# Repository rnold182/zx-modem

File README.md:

# ZX MODEM

A Wi-Fi network modem for an **unmodified ZX Spectrum 48K**. An ESP32 talks
to the Spectrum through its **EAR and MIC tape sockets**, using the
Spectrum's own ROM tape routines in both directions: no hardware changes, no
expansion port, no custom Spectrum audio code.

On top of it runs a small app platform: a menu with a live status line
(network, signal, IP, date and time), a Wi-Fi setup screen on the Spectrum
itself, web fetches from BASIC, and an 8TML browser in progress
([zx-vvv](apps/zx-vvv/)).

**Status:** the modem (Phase 1) works on a real 48K: two-way tape link, menu,
Wi-Fi setup with saved networks, HTTP and HTTPS fetches for BASIC programs.
The browser, zx-vvv, fetches 8TML pages and lays them out itself; links
and colours are next.

## Screenshots

| | |
|---|---|
|  |  |
| **The menu.** Items come from the modem's app list; the status line keeps the time between requests. | **Modem Info:** firmware, protocol, Wi-Fi, address, signal and clock, straight from the modem. |
|  |  |
| **Wi-Fi Setup**, an app the menu downloads: signal bars, padlocks, a tick for the connected network, dots for saved ones. | **Password entry** on the Spectrum's keyboard, masked (CAPS+4 shows it). |
|  |  |
| **Connected:** the modem saves the network and rejoins it by itself. | **From BASIC:** `LET U$="http://wttr.in/..."`, `USR 32771` fetches, `USR 32774` prints. |

*Captured in the Fuse emulator with recorded modem replies standing in for
the ESP32 (so the network names and the time are made up); a real 48K shows
exactly the same screens.*

## Documentation

| Document | For |
|---|---|
| [**ZX Modem Link Protocol 1**](docs/link-protocol.md) | the modem standard: tape signal, packet framing, the registry of services, response types and apps, every command, compatibility rules |
| [**App API**](docs/app-api.md) | writing Spectrum apps and BASIC programs that use the modem: memory map, the fixed call table, a "hello" app, the BASIC `USR` entry points |
| [`sdk/`](sdk/) | the include files apps build against |
| [Hardware](docs/hardware.md) | the carrier board (rev C), connections, pins, revisions |
| [`hardware/DESIGN.md`](hardware/DESIGN.md) | the board's full design notes and simulation |

## How it works

```
   web (HTTP/HTTPS)
        |  Wi-Fi
 +------+--------------------+   EAR (tape signal in)   +-----------------------+
 | ESP32-S3                  | -----------------------> | ZX Spectrum 48K       |
 |  Wi-Fi, TLS, NTP          |                          |  ROM LD-BYTES/SA-BYTES |
 |  tape encoder (RMT)       | <----------------------- |  menu, apps, BASIC    |
 |  tape decoder (edge ISR)  |   MIC (tape signal out)  |                       |
 +---------------------------+                          +-----------------------+
```

The Spectrum saves a short **request** block (`[service][command][args]`); the
modem answers with **header + data** blocks the ROM loader can read. One side
talks at a time. At ROM tape speed that is about 170 bytes/s, so a status
request takes about 6 s and a one-line web reply about 10 s. Details:
[link protocol](docs/link-protocol.md).

## Using it

1. Build the board ([hardware](docs/hardware.md)) or wire an ESP32 dev board
   to the EAR/MIC sockets, and flash the firmware
   ([a release](#flashing-a-release), or [build it](#building)).
2. On the Spectrum type `LOAD ""`, then press **PLAY** on the modem. The
   ZX MODEM menu loads (about 20 s) and shows the modem's status.
3. Menu keys: 6/7 or the cursor keys move, ENTER or a digit chooses, R
   refreshes the status.
4. **Wi-Fi Setup** scans and lists networks (a tick: connected, a dot:
   saved). Pick one and type its password (CAPS+0 delete, CAPS+2 caps lock,
   CAPS+4 show/hide, CAPS+1 back). The modem remembers up to 5 networks and
   joins the strongest one in range by itself.

PLAY button, decided when you let go:

| Hold | Action |
|---|---|
| short | send the menu |
| 2-5 s (LED white) | send a tape test program: it prints a message and `SAVE`s 32 ROM bytes, which the modem checks |
| 5 s or more (LED flashing red) | forget all saved Wi-Fi networks |

LED: blue = sending, yellow = receiving, then green (good) or red (bad).
Idle: a short blink every 2 s, green when Wi-Fi is up, amber while
connecting, purple when no network is set.

### From BASIC

Choose **BASIC** in the menu: the menu stays in memory, and any BASIC program
can fetch a web page through it ([App API §5](docs/app-api.md#5-basic-programs)):

```
10 LET U$="http://wttr.in/Budapest?format=%l:+%C+%t"
20 LET N=USR 32771
30 IF PEEK 32777<>0 THEN PRINT "Error ";PEEK 32777;": ";
40 RANDOMIZE USR 32774
```

`https://` works too (the ESP32 does TLS). `RANDOMIZE USR 32768` goes back to
the menu. A longer example: [`zx/basic/fetchdemo.asm`](zx/basic/fetchdemo.asm).

## zx-vvv, an 8TML browser

[8TML](https://t8wn.com/8tml/) is a tiny markup language for a retro web:
plain ASCII pages, readable on 8-bit machines, a lot like Markdown. **zx-vvv**
is the official ZX Spectrum port of VVV, its reference browser, running
on the 48K through this modem ([`apps/zx-vvv/`](apps/zx-vvv/)). It is
item 1 in the menu. It lays pages out screen for screen the same as the
8TML reference tool, in Spectrum colours, with bold and italic glyphs made
from the ROM font.

- **The Spectrum is the browser:** it resolves links, decides what to
  fetch and refuse, and parses the page itself (headings, paragraphs,
  lists, quotes, preformatted text, emphasis, colour tags, links), laid
  out in 32 columns.
- **Links and history:** 6/7 or the cursor keys move between links, ENTER
  follows one, B goes back to the screen you were on, L lists the page's
  links, G types an address, ? shows all the keys.
- **Stylesheets:** a site's `site.8ss` and a page's own sheet, with
  `zx.` keys for the Spectrum.
- **The modem stays a modem:** a general [http service](docs/link-protocol.md#64-http-0x01)
  does HTTPS, redirects, the content-type filter the browser asks for and
  UTF-8 to ASCII. It knows nothing about 8TML.
- **Tested hard:** every layout is checked against the reference tool,
  and a fuzzer runs the browser's own Z80 code in an emulated 48K on
  thousands of broken pages (`apps/zx-vvv/host/fuzztest.ps1`).
- **Later:** forms. The home page is T8wn's own, served as live 8TML.

A page and how zx-vvv lays it out (the layout comes from the 8TML
reference tool, the browser's test oracle):

```
---                                    Hello from a 48K
8tml: 1
title: My plot                         8TML is plain text with a little
case: mixed                            markup: emphasis, colours, links
---                                    and lists.
# Hello from a 48K
                                       * Parsed on the Spectrum itself
8TML is plain text with a little       * 32 columns, Spectrum colours
markup: *emphasis*, <yellow>colours</>,
[links](news.8tml) and lists.

* Parsed on the Spectrum itself
* 32 columns, Spectrum colours
```

## Flashing a release

[Releases](https://github.com/rnold182/zx-modem/releases) have the firmware
for the **ESP32-S3** (the SuperMini on the carrier board) ready to flash,
with the menu, Wi-Fi Setup and zx-vvv built in. No Wi-Fi network is built
in: you choose one from the Spectrum (Wi-Fi Setup in the menu).

| File | What |
|---|---|
| `zx-modem-<version>-esp32s3.bin` | the whole flash: for a first install. **Erases saved Wi-Fi networks.** |
| `zx-modem-<version>-esp32s3-app.bin` | the firmware alone: for updating, keeps saved networks |
| `SHA256SUMS.txt` | checksums |

Connect the board with USB. If the computer doesn't find it, hold **BOOT**
on the SuperMini while plugging it in (that starts its USB loader), then
let go.

**In the browser** (Chrome or Edge, which can talk to serial ports):

1. Open [Espressif's web flasher](https://espressif.github.io/esptool-js/),
   set the baud rate to 460800 and click **Connect**, then pick the board's
   port.
2. First install: choose `zx-modem-<version>-esp32s3.bin` at flash address
   **0x0**. Update: `zx-modem-<version>-esp32s3-app.bin` at **0x10000**.
3. Click **Program**, wait for it to finish, then press **RESET** on the
   board (or unplug it and plug it back in).

**From the command line**, with [esptool](https://docs.espressif.com/projects/esptool/)
(`pip install esptool`), `COM5` being your port (`/dev/ttyACM0` on Linux,
`/dev/cu.usbmodem…` on a Mac):

```
esptool.py --chip esp32s3 -p COM5 -b 460800 write_flash 0x0 zx-modem-0.8-esp32s3.bin
esptool.py --chip esp32s3 -p COM5 -b 460800 write_flash 0x10000 zx-modem-0.8-esp32s3-app.bin
```

The first line is a first install, the second an update (esptool 5 also
takes `esptool` and `write-flash`). Then on the Spectrum: `LOAD ""` and PLAY
on the modem ([Using it](#using-it)). The menu's status screen shows the
firmware version. A classic ESP32 dev board needs a build of its own (below).

## Building

### Firmware (ESP32)

ESP-IDF 5.3 or newer (5.5.1 is what it's tested with). In the `esp32` folder:

```
idf.py set-target esp32s3     # ESP32-S3 SuperMini on the carrier board
idf.py build
idf.py -p COM5 flash monitor  # your serial port
```

`idf.py set-target esp32` builds for a classic ESP32 dev board instead (TX
GPIO25, RX GPIO26, the BOOT button as PLAY). The firmware build assembles the
Spectrum menu and apps itself, so it needs
[sjasmplus](https://github.com/z00m128/sjasmplus) on the path. A Wi-Fi
network can also be preset in `idf.py menuconfig` (ZX modem); it is only
used until one is saved from the Spectrum.

### Host tests and Spectrum programs

CMake, a C compiler and Ninja; sjasmplus for the Spectrum programs. From
the repository root (not `esp32/`):

```
cmake -S . -B build -G Ninja
cmake --build build
ctest --test-dir build
```

This runs the tape encoder/decoder tests (including a real 48K `SAVE`
recording), the UTF-8 converter tests, and writes `build/zxmenu.tap`,
`build/wifisetup.bin` and `build/fetchdemo.tap`.

### Trying Spectrum programs in an emulator

An emulator such as [Fuse](https://fuse-emulator.sourceforge.net/) can't
answer the modem's requests, so append a canned reply for each request the
program makes, in order:

```
python host/tools/fake_reply.py build/zxmenu.tap build/session.tap info:HomeNet overlay:build/wifisetup.bin "netlist:HomeNet/-52/3/3,Cafe/-80/0" info:HomeNet
```

Load `session.tap` in the emulator: the menu, then Wi-Fi Setup, run on the
canned answers.

## Repository layout

| Path | What |
|---|---|
| `docs/` | the protocol standard, the app API, hardware notes |
| `sdk/` | include files for apps |
| `esp32/` | the ESP-IDF firmware (link, Wi-Fi/NTP, fetch, app registry, tape I/O) |
| `components/` | portable C shared by firmware and host: `tape` (encoder/decoder), `translit` (UTF-8 to ASCII) |
| `zx/` | Spectrum code inside the menu (`lib/`, `menu/`), BASIC examples (`basic/`), the first test program (`modemtest/`) |
| `apps/` | Spectrum apps: `wifisetup/` (app 1), `zx-vvv/` (the browser, its own project) |
| `host/` | host tests and `tools/fake_reply.py` |
| `hardware/` | the carrier PCB: KiCad project, generator scripts, BOM/CPL, design notes |

`CLAUDE.md` is the project brief used with Claude Code; it doubles as the
detailed design document.

## Credits

- 8TML and the reference client VVV are by the T8wn project
  ([t8wn.com](https://t8wn.com/8tml/)); zx-vvv is their official ZX Spectrum
  port.
- The planned AT command service follows
  [Zimodem](https://github.com/bozimmerman/Zimodem) by Bo Zimmerman.
- ROM routine addresses were checked against
  [the 48K ROM disassembly](https://skoolkid.github.io/rom/).
- zx-vvv's fuzzer runs on Andre Weissflog's Z80 emulator from
  [floooh/chips](https://github.com/floooh/chips) (zlib licence,
  `host/third_party/chips/`).

## License

[MIT](LICENSE), for the code, documentation and hardware files in this
repository. The 8TML specification package is not included (see
[`apps/zx-vvv/spec/`](apps/zx-vvv/spec/GET-THE-SPEC.md)).

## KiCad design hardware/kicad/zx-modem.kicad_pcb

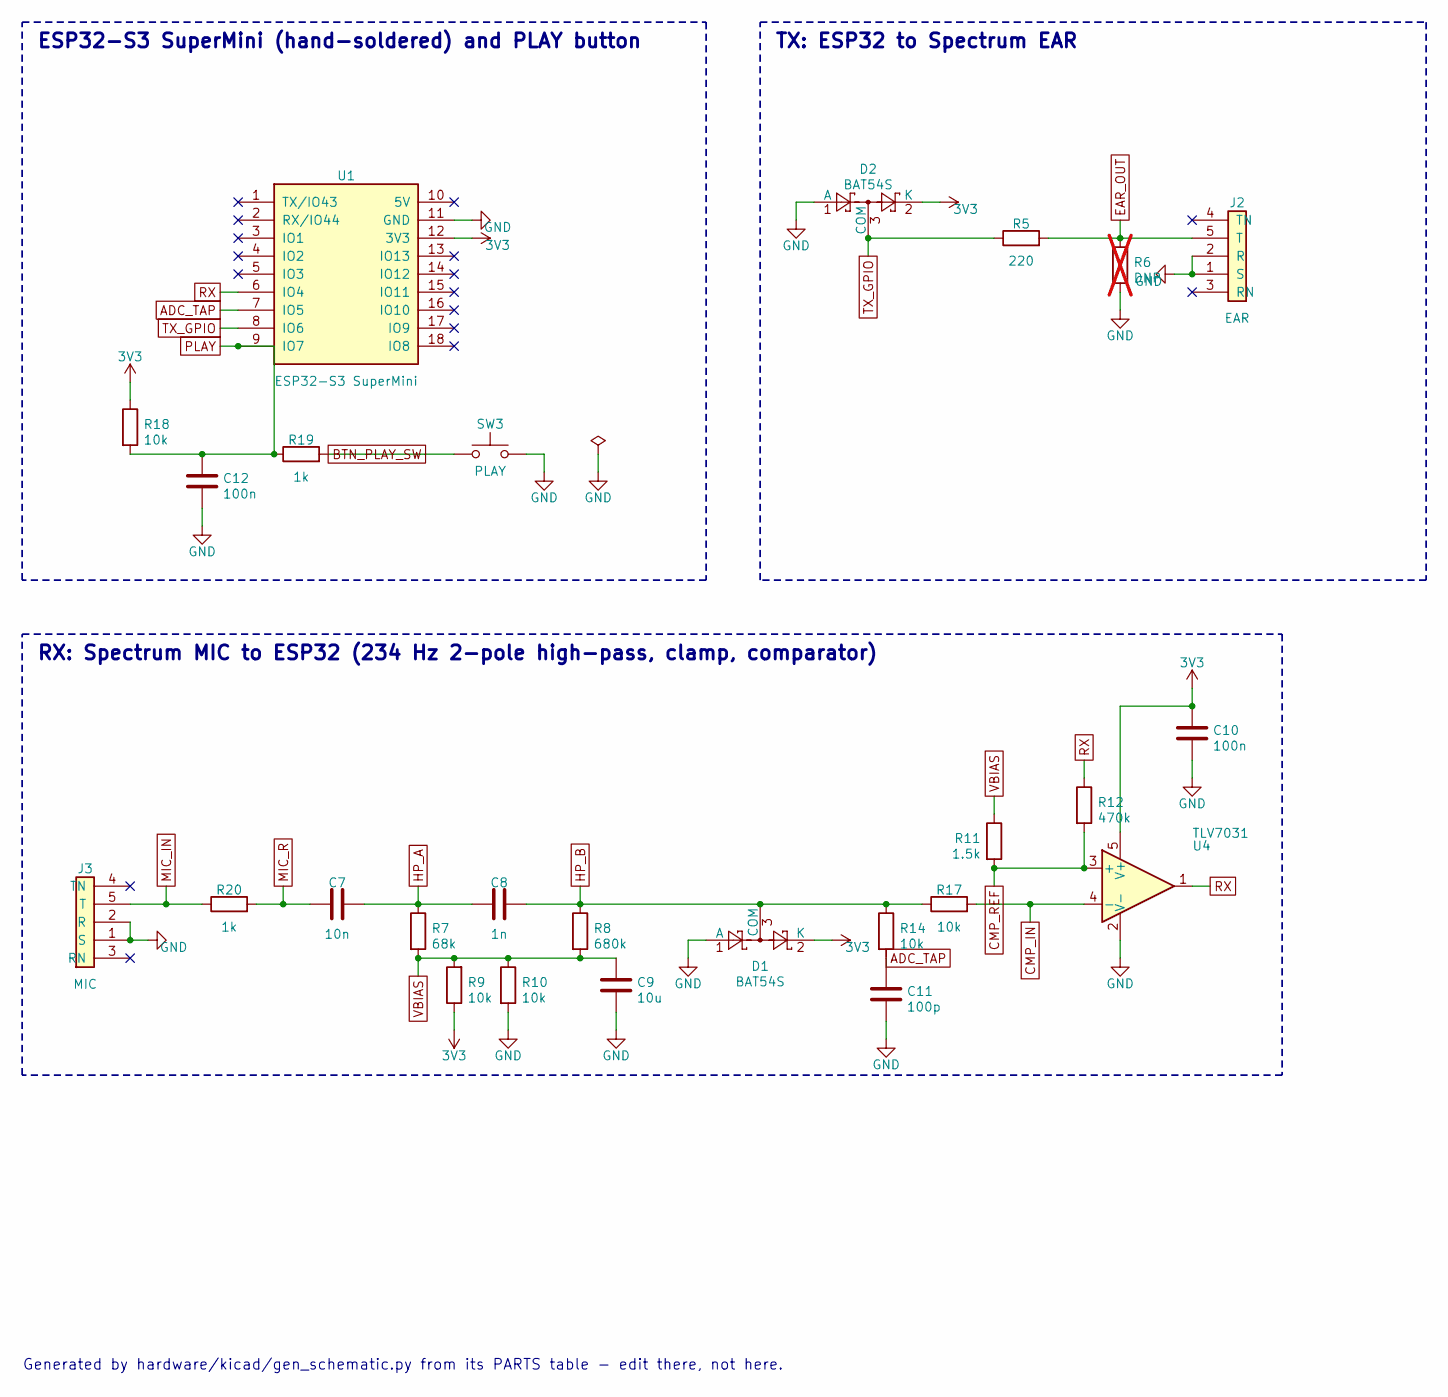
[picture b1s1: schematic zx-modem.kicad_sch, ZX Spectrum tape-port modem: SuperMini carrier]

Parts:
C7: 10n; C_0805_2012Metric; LCSC C1710
C8: 1n; C_0805_2012Metric; LCSC C51210
C9: 10u; C_0805_2012Metric; LCSC C15850
C10, C12: 100n; C_0805_2012Metric; LCSC C49678
C11: 100p; C_0805_2012Metric; LCSC C1790
D1, D2: BAT54S; SOT-23; LCSC C47546
J2: EAR; PJ-307; LCSC C2939173
J3: MIC; PJ-307; LCSC C2939173
R5: 220; R_0805_2012Metric; LCSC C17557
R6: DNP; R_0805_2012Metric; not fitted
R7: 68k; R_0805_2012Metric; LCSC C17801
R8: 680k; R_0805_2012Metric; LCSC C17797
R9, R10, R14, R17, R18: 10k; R_0805_2012Metric; LCSC C17414
R11: 1.5k; R_0805_2012Metric; LCSC C4310
R12: 470k; R_0805_2012Metric; LCSC C17709
R19, R20: 1k; R_0805_2012Metric; LCSC C17513
SW3: PLAY; SW_Push_1P1T_XKB_TS-1187A; LCSC C318884
U1: ESP32-S3 SuperMini; ESP32-S3-SuperMini
U4: TLV7031; SOT-23-5; LCSC C2869832

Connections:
3V3: C10.1, D1.2 (K), D2.2 (K), R9.1, R18.1, U1.12 (3V3), U4.5 (V+)
ADC_TAP: C11.1, R14.2, U1.7 (IO5)
BTN_PLAY_SW: R19.2, SW3.1
CMP_IN: R17.2, U4.4 (-)
CMP_REF: R11.2, R12.2, U4.3 (+)
EAR_OUT: J2.5 (T), R5.2, R6.1
GND: C9.2, C10.2, C11.2, C12.2, D1.1 (A), D2.1 (A), J2.1 (S), J2.2 (R), J3.1 (S), J3.2 (R), R6.2, R10.2, SW3.2, U1.11 (GND), U4.2 (V-)
HP_A: C7.2, C8.1, R7.1
HP_B: C8.2, D1.3 (COM), R8.1, R14.1, R17.1
MIC_IN: J3.5 (T), R20.1
MIC_R: C7.1, R20.2
PLAY: C12.1, R18.2, R19.1, U1.9 (IO7)
RX: R12.1, U1.6 (IO4), U4.1
TX_GPIO: D2.3 (COM), R5.1, U1.8 (IO6)
VBIAS: C9.1, R7.2, R8.2, R9.2, R10.1, R11.1

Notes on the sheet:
ESP32-S3 SuperMini (hand-soldered) and PLAY button
TX: ESP32 to Spectrum EAR
RX: Spectrum MIC to ESP32 (234 Hz 2-pole high-pass, clamp, comparator)
Generated by hardware/kicad/gen_schematic.py from its PARTS table - edit there, not here.

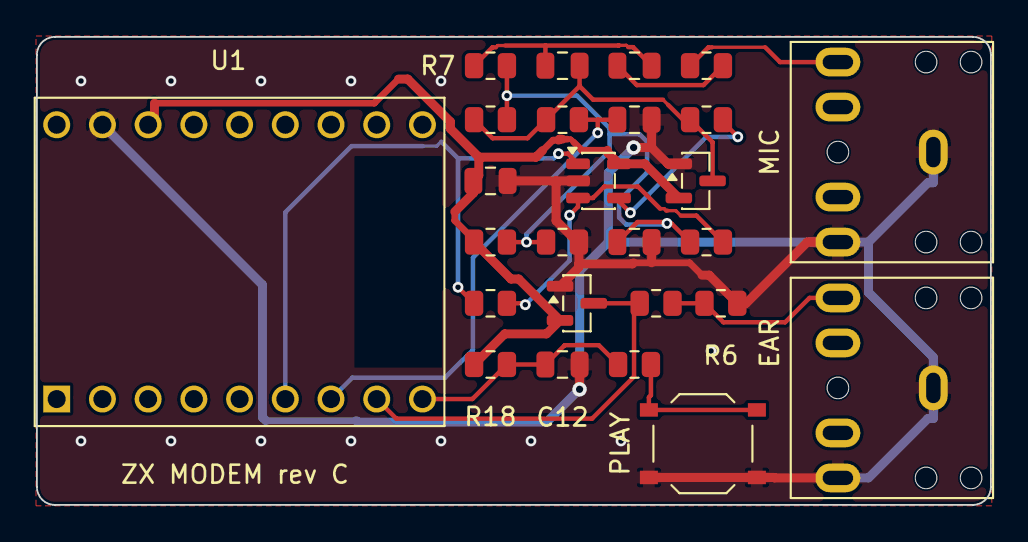
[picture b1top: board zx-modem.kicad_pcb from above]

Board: 2 copper layers, 53.0 x 26.0 mm, 26 parts (0 on the bottom side), 15 nets.

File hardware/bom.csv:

Part,Designator,Footprint,LCSC Part #,Fitted by
ESP32-S3 SuperMini (pinout per espboards.dev),U1,ESP32-S3-SuperMini,,hand-solder
10k,"R18,R17,R14,R9,R10",R_0805_2012Metric,C17414,JLCPCB
100n,"C12,C10",C_0805_2012Metric,C49678,JLCPCB
1k,"R19,R20",R_0805_2012Metric,C17513,JLCPCB
PLAY,SW3,SW_Push_1P1T_XKB_TS-1187A,C318884,JLCPCB
BAT54S,"D2,D1",SOT-23,C47546,JLCPCB
220,R5,R_0805_2012Metric,C17557,JLCPCB
DNP,R6,R_0805_2012Metric,,DNP
"PJ-307 3.5 mm jack (5-pin, through-hole), HOOYA","J2,J3",PJ-307,C2939173,JLCPCB THT (wave solder)
10n,C7,C_0805_2012Metric,C1710,JLCPCB
68k,R7,R_0805_2012Metric,C17801,JLCPCB
1n,C8,C_0805_2012Metric,C51210,JLCPCB
680k,R8,R_0805_2012Metric,C17797,JLCPCB
100p,C11,C_0805_2012Metric,C1790,JLCPCB
TLV7031,U4,SOT-23-5,C2869832,JLCPCB
470k,R12,R_0805_2012Metric,C17709,JLCPCB
1.5k,R11,R_0805_2012Metric,C4310,JLCPCB
10u,C9,C_0805_2012Metric,C15850,JLCPCB

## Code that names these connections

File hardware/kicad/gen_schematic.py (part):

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PARTS = {
    # --- ESP32-S3 SuperMini and the PLAY button ---------------------------------------
    'U1': ('zx-modem:ESP32-S3-SuperMini', 'ESP32-S3 SuperMini', 'zx-modem:ESP32-S3-SuperMini', '',
           {'6': 'RX', '7': 'ADC_TAP', '8': 'TX_GPIO', '9': 'PLAY', '11': 'GND', '12': '3V3'},
           (20, 20, 0), {'hand': True, 'mpn': 'ESP32-S3 SuperMini (pinout per espboards.dev)'}),
    'R18': ('Device:R', '10k', R0805, 'C17414', {'1': '3V3', '2': 'PLAY'}, (8, 28.5, 0), {}),
    'C12': ('Device:C', '100n', C0805, 'C49678', {'1': 'PLAY', '2': 'GND'}, (12, 31.5, 0), {}),
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            {'1': 'BTN_PLAY_SW', '2': 'GND'}, (28, 30, 0), {}),
    # --- TX to EAR -------------------------------------------------------------------
    'D2': ('Diode:BAT54S', 'BAT54S', 'Package_TO_SOT_SMD:SOT-23', 'C47546',
           {'1': 'GND', '2': '3V3', '3': 'TX_GPIO'}, (49, 16, 0), {}),
    'R5': ('Device:R', '220', R0805, 'C17557', {'1': 'TX_GPIO', '2': 'EAR_OUT'}, (57.5, 18, 90), {}),
    'R6': ('Device:R', 'DNP', R0805, '', {'1': 'EAR_OUT', '2': 'GND'}, (63, 19.5, 0), {'dnp': True}),
    # PJ-307 jacks as JLCPCB fits them (HOOYA PJ-307, C2939173, wave soldered; our footprint
    # is drawn from theirs). Pinout measured on rev B boards: 1 sleeve, 5 tip, 2 ring; 3 and 4
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    for net, qs in nets.items():
        groups = {}
        for q in qs: groups.setdefault(q['grp'], []).append(q)
        # A fully wired signal net still gets one label: it names the net (HP_A, EN...) for the
        # reader, and KiCad would otherwise invent a name the board doesn't use.
        for g in groups.values():
            done = False
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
